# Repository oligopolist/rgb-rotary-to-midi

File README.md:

# rgb-rotary-to-midi
A midi box using a teensy3.2 and sparkfun RGB encoders controlled by ws2811's

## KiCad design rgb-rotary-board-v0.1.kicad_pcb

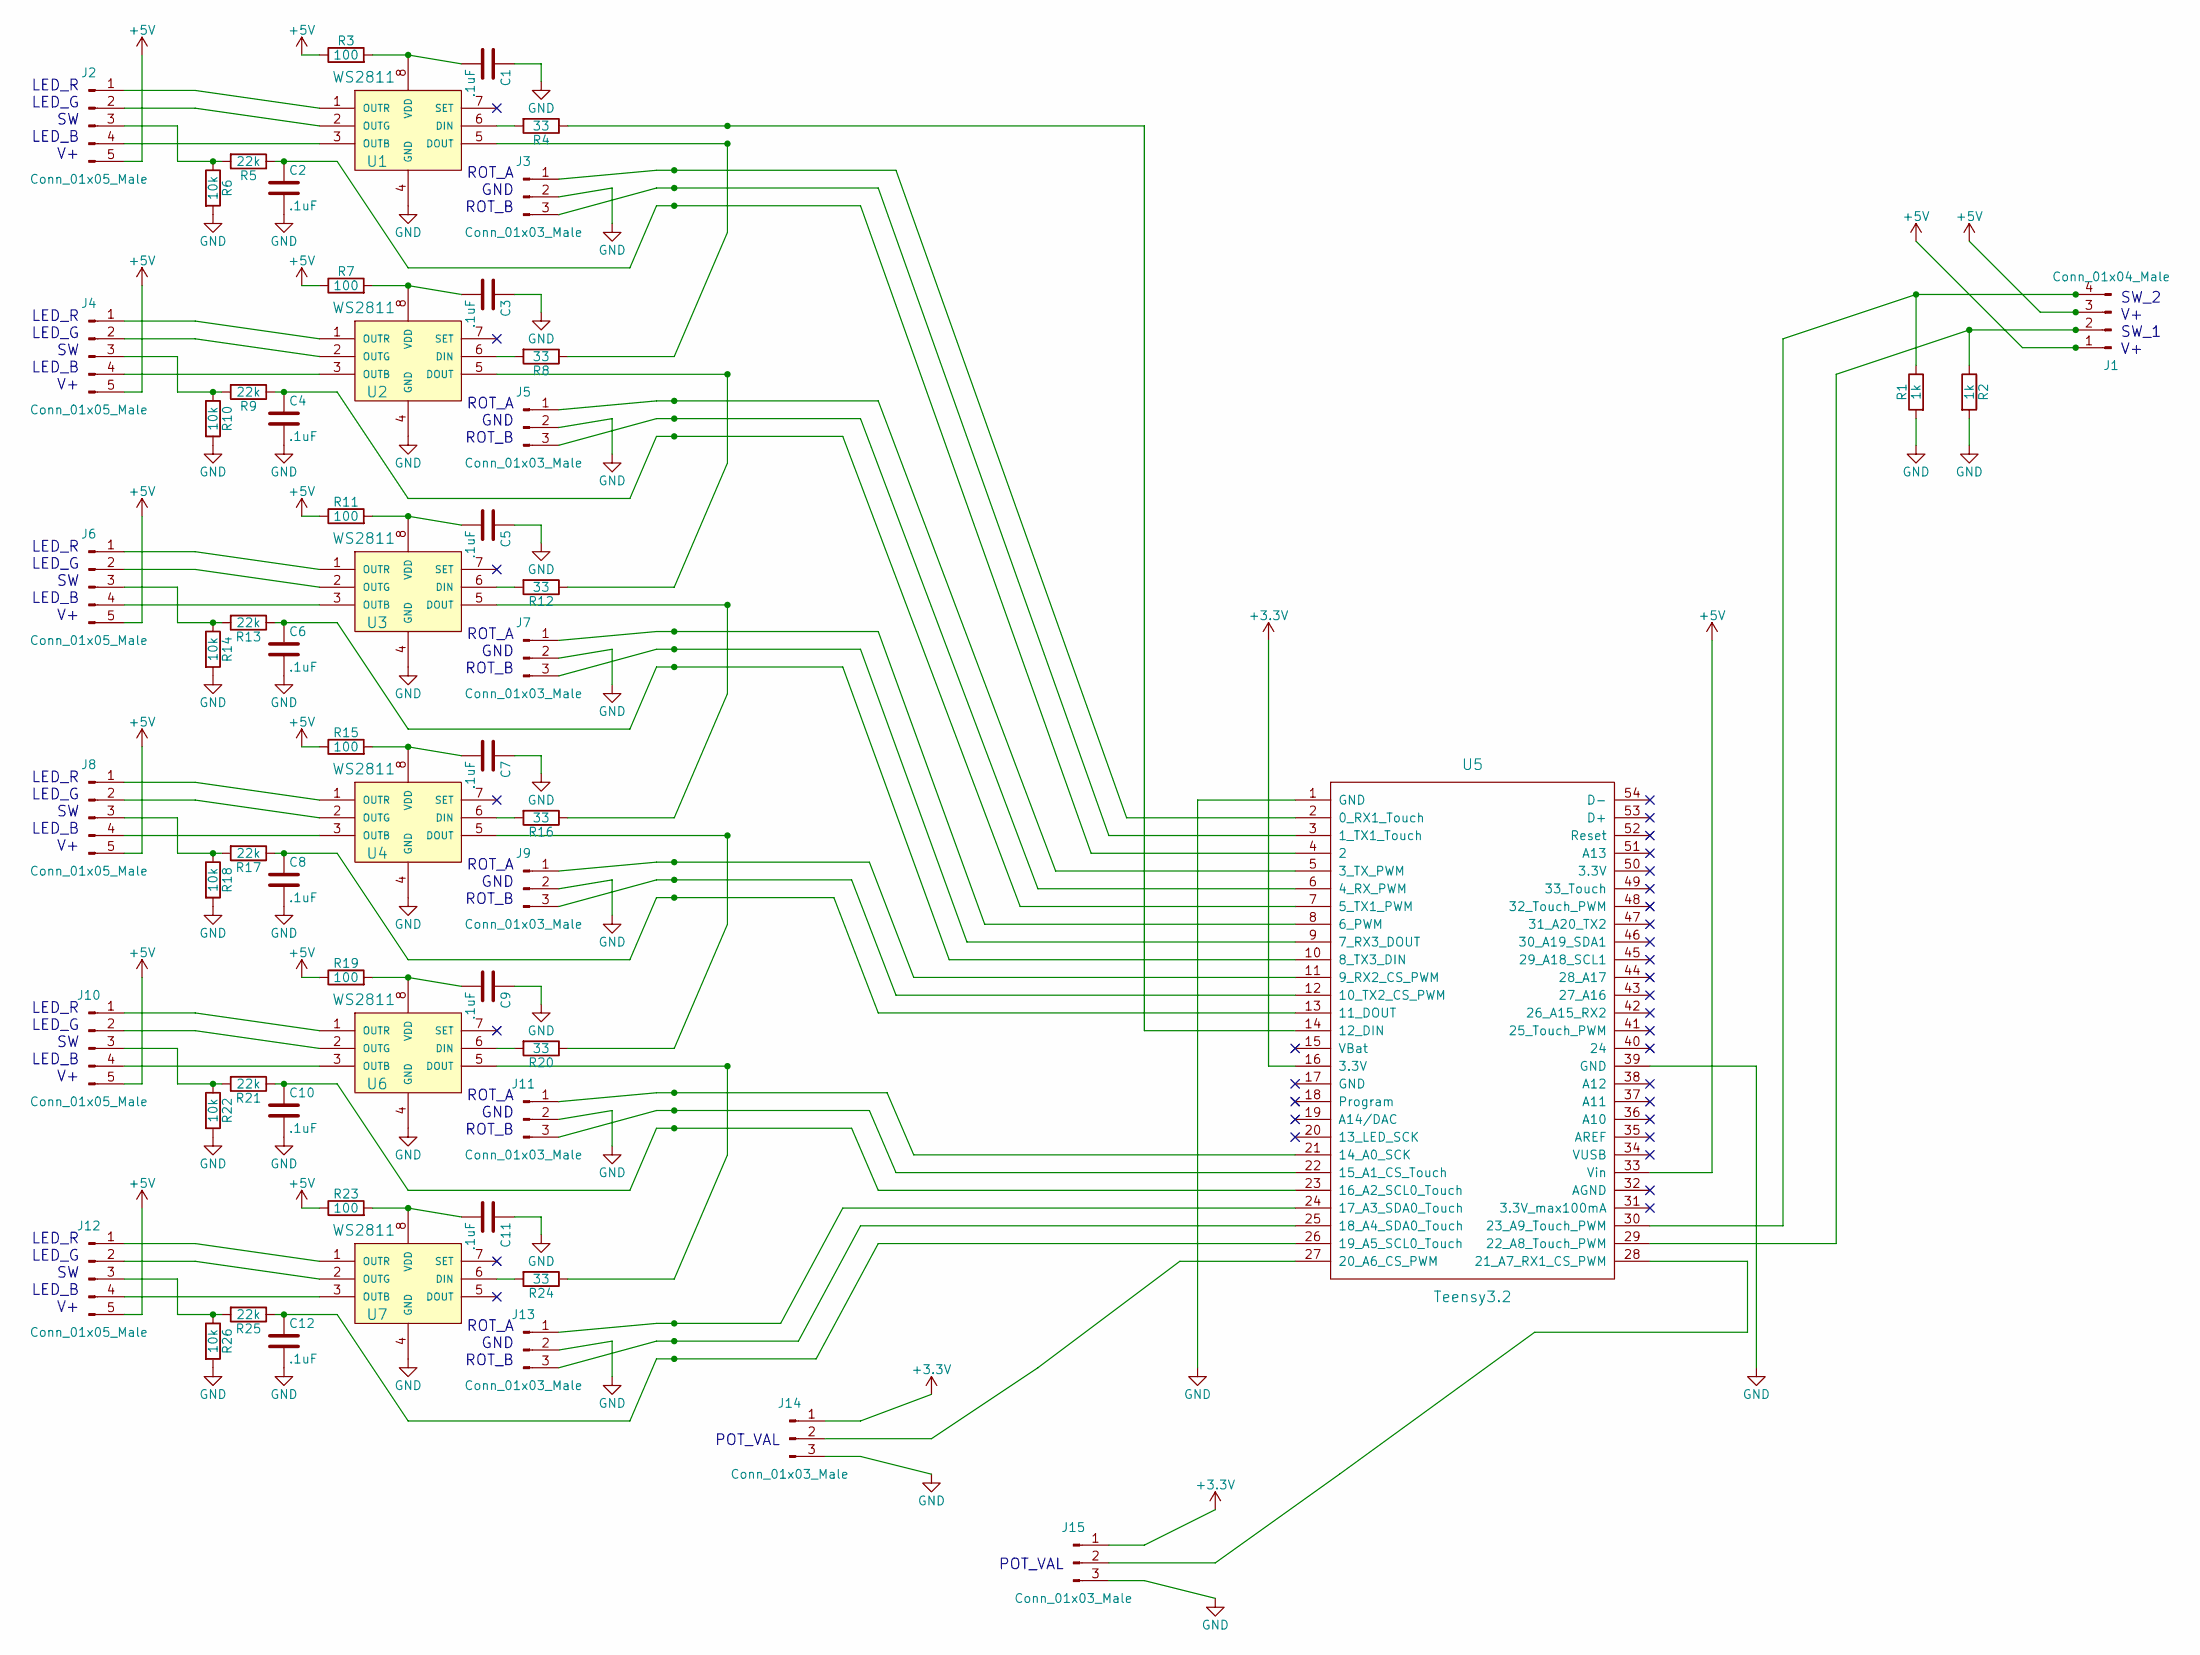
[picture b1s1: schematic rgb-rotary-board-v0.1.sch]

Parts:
C1, C2: .1uF; C_Disc_D5.0mm_W2.5mm_P2.50mm
C3, C4, C5, C6, C7, C8, C9, C10, C11, C12: .1uF; C_Disc_D5.0mm_W2.5mm_P5.00mm
J1: Conn_01x04_Male; Pin_Header_Straight_1x04_Pitch2.54mm
J2, J4, J6, J8, J10, J12: Conn_01x05_Male; Pin_Header_Straight_1x05_Pitch2.54mm
J3, J5, J7, J9, J11, J13, J14, J15: Conn_01x03_Male; Pin_Header_Straight_1x03_Pitch2.54mm
R1, R2: 1k; R_Axial_DIN0207_L6.3mm_D2.5mm_P2.54mm_Vertical
R3, R7, R11, R15, R19: 100; R_Axial_DIN0207_L6.3mm_D2.5mm_P2.54mm_Vertical
R4, R8, R12, R16, R20: 33; R_Axial_DIN0207_L6.3mm_D2.5mm_P2.54mm_Vertical
R5, R9, R13, R17, R21: 22k; R_Axial_DIN0207_L6.3mm_D2.5mm_P2.54mm_Vertical
R6, R10, R14, R18: 10k; R_Axial_DIN0207_L6.3mm_D2.5mm_P2.54mm_Vertical
R22, R26: 10k; R_Axial_DIN0207_L6.3mm_D2.5mm_P5.08mm_Vertical
R23: 100; R_Axial_DIN0207_L6.3mm_D2.5mm_P5.08mm_Vertical
R24: 33; R_Axial_DIN0207_L6.3mm_D2.5mm_P5.08mm_Vertical
R25: 22k; R_Axial_DIN0207_L6.3mm_D2.5mm_P5.08mm_Vertical
U1, U2, U3, U4, U6, U7: WS2811; TSOT-23-8_HandSoldering
U5: Teensy3.2; Teensy30_31_32_LC

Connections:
+3V3: J14.1, J15.1, U5.16 (3.3V)
+5V: J1.1, J1.3, J2.5, J4.5, J6.5, J8.5, J10.5, J12.5, R3.1, R7.1, R11.1, R15.1, R19.1, R23.1, U5.33 (Vin)
GND: C1.1, C2.2, C3.1, C4.2, C5.1, C6.2, C7.1, C8.2, C9.1, C10.2, C11.1, C12.2, J3.2, J5.2, J7.2, J9.2, J11.2, J13.2, J14.3, J15.3, R1.2, R2.2, R6.2, R10.2, R14.2, R18.2, R22.2, R26.2, U1.4 (GND), U2.4 (GND), U3.4 (GND), U4.4 (GND), U5.1 (GND), U5.39 (GND), U6.4 (GND), U7.4 (GND)
unnamed: C1.2, R3.2, U1.8 (VDD)
unnamed: C2.1, R5.1, U5.4 (2)
unnamed: C3.2, R7.2, U2.8 (VDD)
unnamed: C4.1, R9.1, U5.7 (5_TX1_PWM)
unnamed: C5.2, R11.2, U3.8 (VDD)
unnamed: C6.1, R13.1, U5.10 (8_TX3_DIN)
unnamed: C7.2, R15.2, U4.8 (VDD)
unnamed: C8.1, R17.1, U5.13 (11_DOUT)
unnamed: C9.2, R19.2, U6.8 (VDD)
unnamed: C10.1, R21.1, U5.23 (16_A2_SCL0_Touch)
unnamed: C11.2, R23.2, U7.8 (VDD)
unnamed: C12.1, R25.1, U5.26 (19_A5_SCL0_Touch)
unnamed: J1.2, R2.1, U5.29 (22_A8_Touch_PWM)
unnamed: J1.4, R1.1, U5.30 (23_A9_Touch_PWM)
unnamed: J2.1, U1.1 (OUTR)
unnamed: J2.2, U1.2 (OUTG)
unnamed: J2.3, R5.2, R6.1
unnamed: J2.4, U1.3 (OUTB)
unnamed: J3.1, U5.2 (0_RX1_Touch)
unnamed: J3.3, U5.3 (1_TX1_Touch)
unnamed: J4.1, U2.1 (OUTR)
unnamed: J4.2, U2.2 (OUTG)
unnamed: J4.3, R9.2, R10.1
unnamed: J4.4, U2.3 (OUTB)
unnamed: J5.1, U5.5 (3_TX_PWM)
unnamed: J5.3, U5.6 (4_RX_PWM)
unnamed: J6.1, U3.1 (OUTR)
unnamed: J6.2, U3.2 (OUTG)
unnamed: J6.3, R13.2, R14.1
unnamed: J6.4, U3.3 (OUTB)
unnamed: J7.1, U5.8 (6_PWM)
unnamed: J7.3, U5.9 (7_RX3_DOUT)
unnamed: J8.1, U4.1 (OUTR)
unnamed: J8.2, U4.2 (OUTG)
unnamed: J8.3, R17.2, R18.1
unnamed: J8.4, U4.3 (OUTB)
unnamed: J9.1, U5.11 (9_RX2_CS_PWM)
unnamed: J9.3, U5.12 (10_TX2_CS_PWM)
unnamed: J10.1, U6.1 (OUTR)
unnamed: J10.2, U6.2 (OUTG)
unnamed: J10.3, R21.2, R22.1
unnamed: J10.4, U6.3 (OUTB)
unnamed: J11.1, U5.21 (14_A0_SCK)
unnamed: J11.3, U5.22 (15_A1_CS_Touch)
unnamed: J12.1, U7.1 (OUTR)
unnamed: J12.2, U7.2 (OUTG)
unnamed: J12.3, R25.2, R26.1
unnamed: J12.4, U7.3 (OUTB)
unnamed: J13.1, U5.24 (17_A3_SDA0_Touch)
unnamed: J13.3, U5.25 (18_A4_SDA0_Touch)
unnamed: J14.2, U5.27 (20_A6_CS_PWM)
unnamed: J15.2, U5.28 (21_A7_RX1_CS_PWM)
unnamed: R4.1, U5.14 (12_DIN)
unnamed: R4.2, U1.6 (DIN)
unnamed: R8.1, U1.5 (DOUT)
unnamed: R8.2, U2.6 (DIN)
unnamed: R12.1, U2.5 (DOUT)
unnamed: R12.2, U3.6 (DIN)
unnamed: R16.1, U3.5 (DOUT)
unnamed: R16.2, U4.6 (DIN)
unnamed: R20.1, U4.5 (DOUT)
unnamed: R20.2, U6.6 (DIN)
unnamed: R24.1, U6.5 (DOUT)
unnamed: R24.2, U7.6 (DIN)

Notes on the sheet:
LED_R LED_G SW LED_B V+
ROT_A GND ROT_B
SW_2 V+ SW_1 V+
POT_VAL

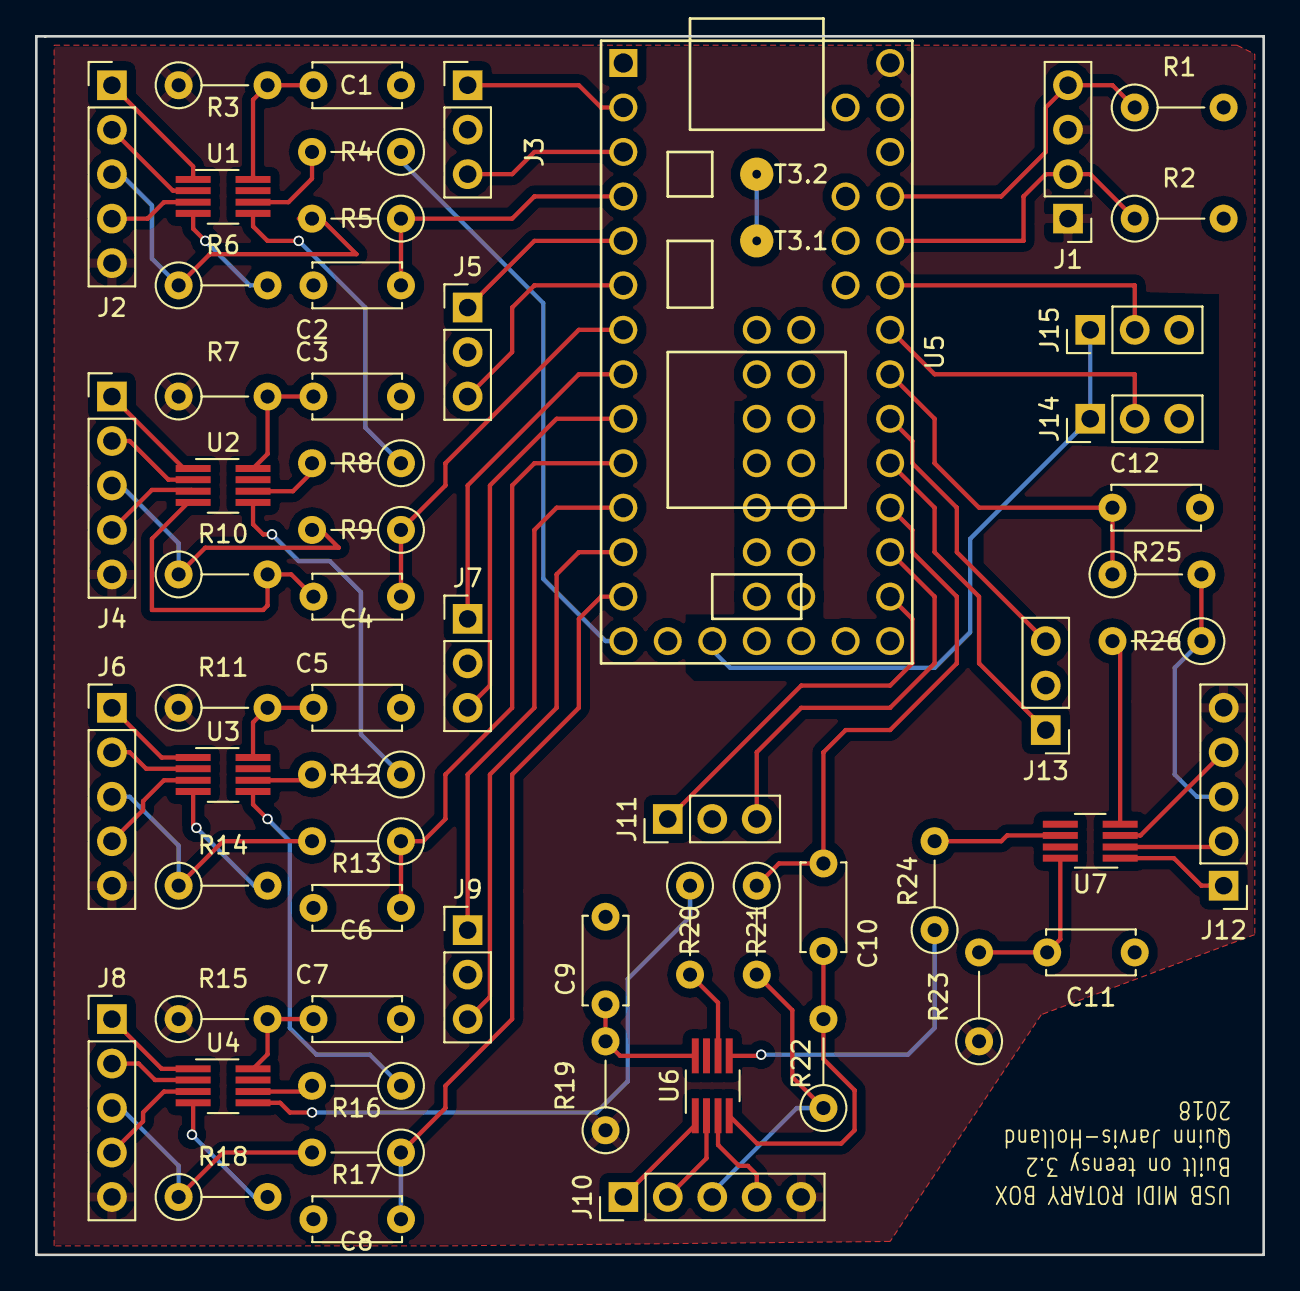
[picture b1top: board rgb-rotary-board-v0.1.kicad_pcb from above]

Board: 2 copper layers, 70.1 x 69.6 mm, 60 parts (0 on the bottom side), 67 nets.
